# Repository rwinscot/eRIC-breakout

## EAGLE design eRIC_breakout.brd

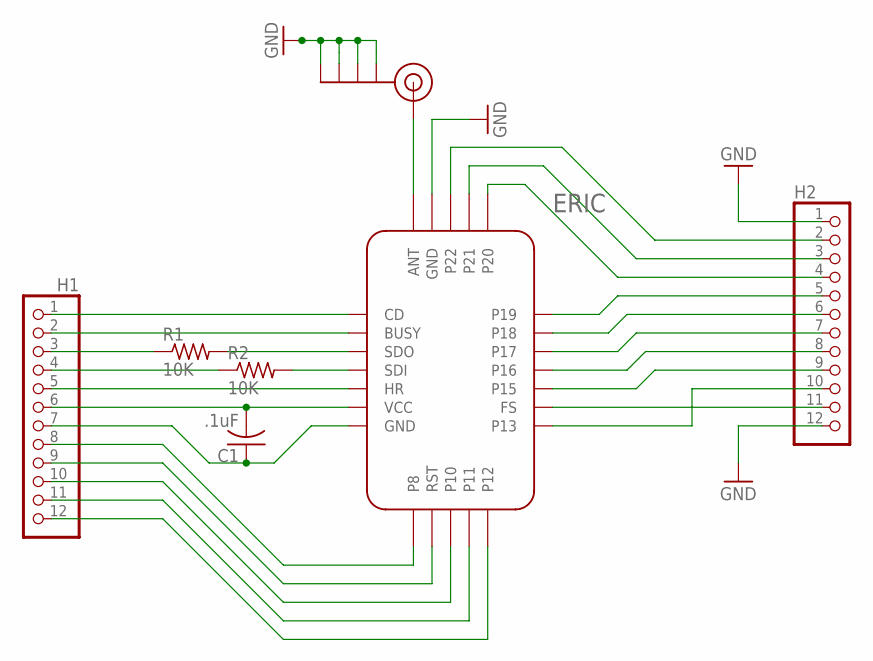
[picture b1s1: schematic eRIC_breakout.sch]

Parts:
C1: .1uF; C0603K
ERIC: ERIC
H1, H2: PINHD-1X12-CB; 1X12-CB
J$1: SMA_EDGE; SMA-EDGE
R1, R2: 10K; R0603

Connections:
GND: C1.1, ERIC.AGND (GND), ERIC.GND, H1.7, H2.1, H2.12, J$1.GND@0 (GND), J$1.GND@1 (GND), J$1.GND@2 (GND), J$1.GND@3 (GND)
unnamed: ERIC.CD, H1.1
unnamed: ERIC.BUSY, H1.2
unnamed: ERIC.ANT, J$1.SIG (SIGNAL)
unnamed: ERIC.HR, H1.5
unnamed: ERIC.E8 (P8), H1.8
unnamed: ERIC.E9 (RST), H1.9
unnamed: ERIC.E10 (P10), H1.10
unnamed: ERIC.E11 (P11), H1.11
unnamed: ERIC.E12 (P12), H1.12
unnamed: ERIC.E15 (P15), H2.9
unnamed: ERIC.E16 (P16), H2.8
unnamed: ERIC.E17 (P17), H2.7
unnamed: ERIC.E18 (P18), H2.6
unnamed: ERIC.E19 (P19), H2.5
unnamed: ERIC.E20 (P20), H2.4
unnamed: ERIC.E21 (P21), H2.3
unnamed: ERIC.E22 (P22), H2.2
unnamed: ERIC.FS, H2.11
unnamed: ERIC.E13 (P13), H2.10
SDI: ERIC.SDI, H1.4, R2.1, R2.2
SDO: ERIC.SDO, H1.3, R1.1, R1.2
VCC: C1.2, ERIC.VCC, H1.6

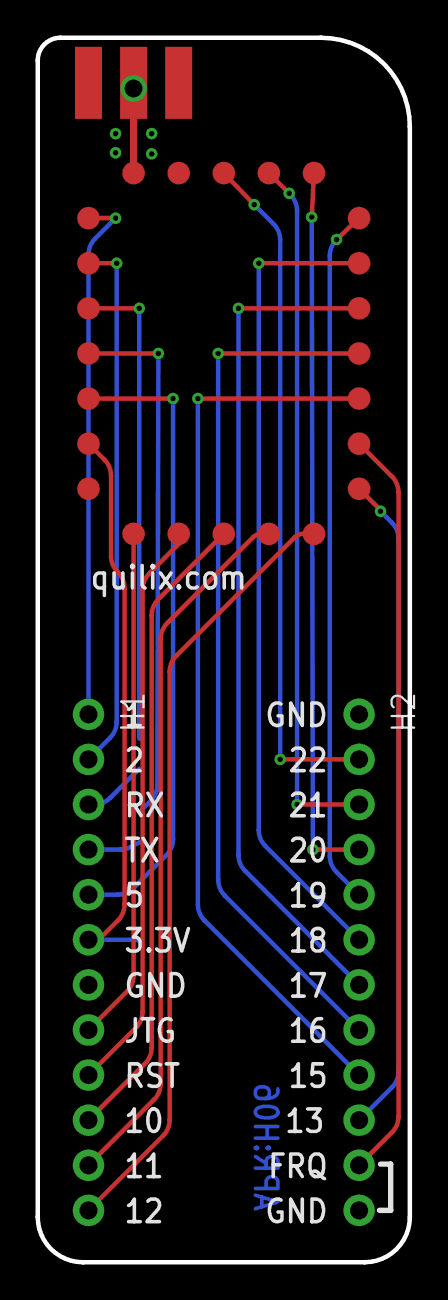
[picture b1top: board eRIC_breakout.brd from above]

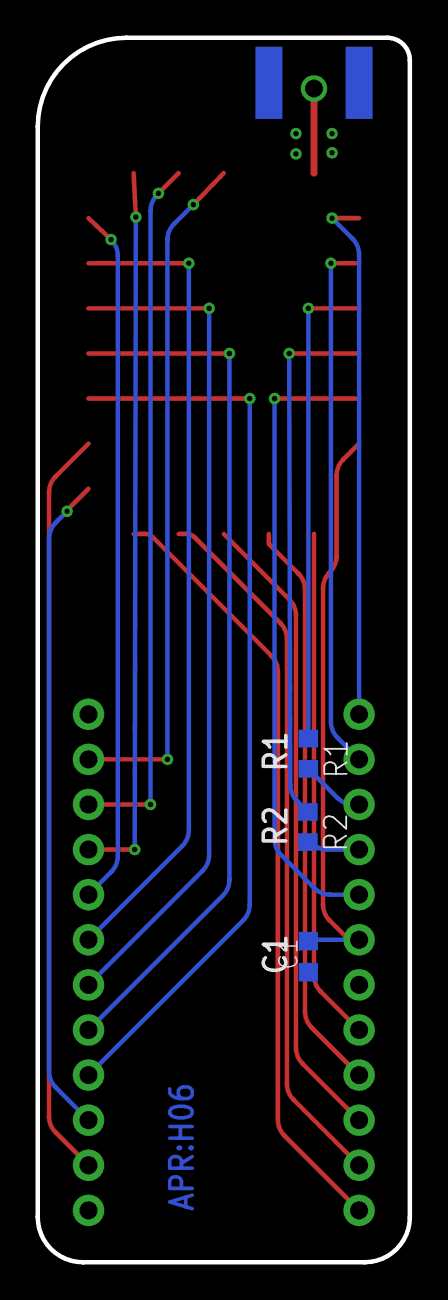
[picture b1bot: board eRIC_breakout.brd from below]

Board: 2 copper layers, 21.0 x 69.0 mm, 7 parts (3 on the bottom side), 23 nets.

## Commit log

2015-04-09 BOM, component names and values
2015-04-09 component values
2015-04-18 overhaul of design, include schematic, un-tested
2015-04-18 OSH Park DRU and CAM processor for Eagle 7.2
2015-04-18 v1.6 ordered 4/18/2015
2015-04-18 BOM updated
2015-04-24 SMA GND schematic changes and IC name added

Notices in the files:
parts and their libraries:
SparkFun-Connectors: Licensing: Creative Commons ShareAlike 4.0 International - https://creativecommons.org/licenses/by-sa/4.0
